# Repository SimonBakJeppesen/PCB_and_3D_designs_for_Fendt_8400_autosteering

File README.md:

# 3D_designs_for_Fendt_8400_autosteering
PCB and 3D design

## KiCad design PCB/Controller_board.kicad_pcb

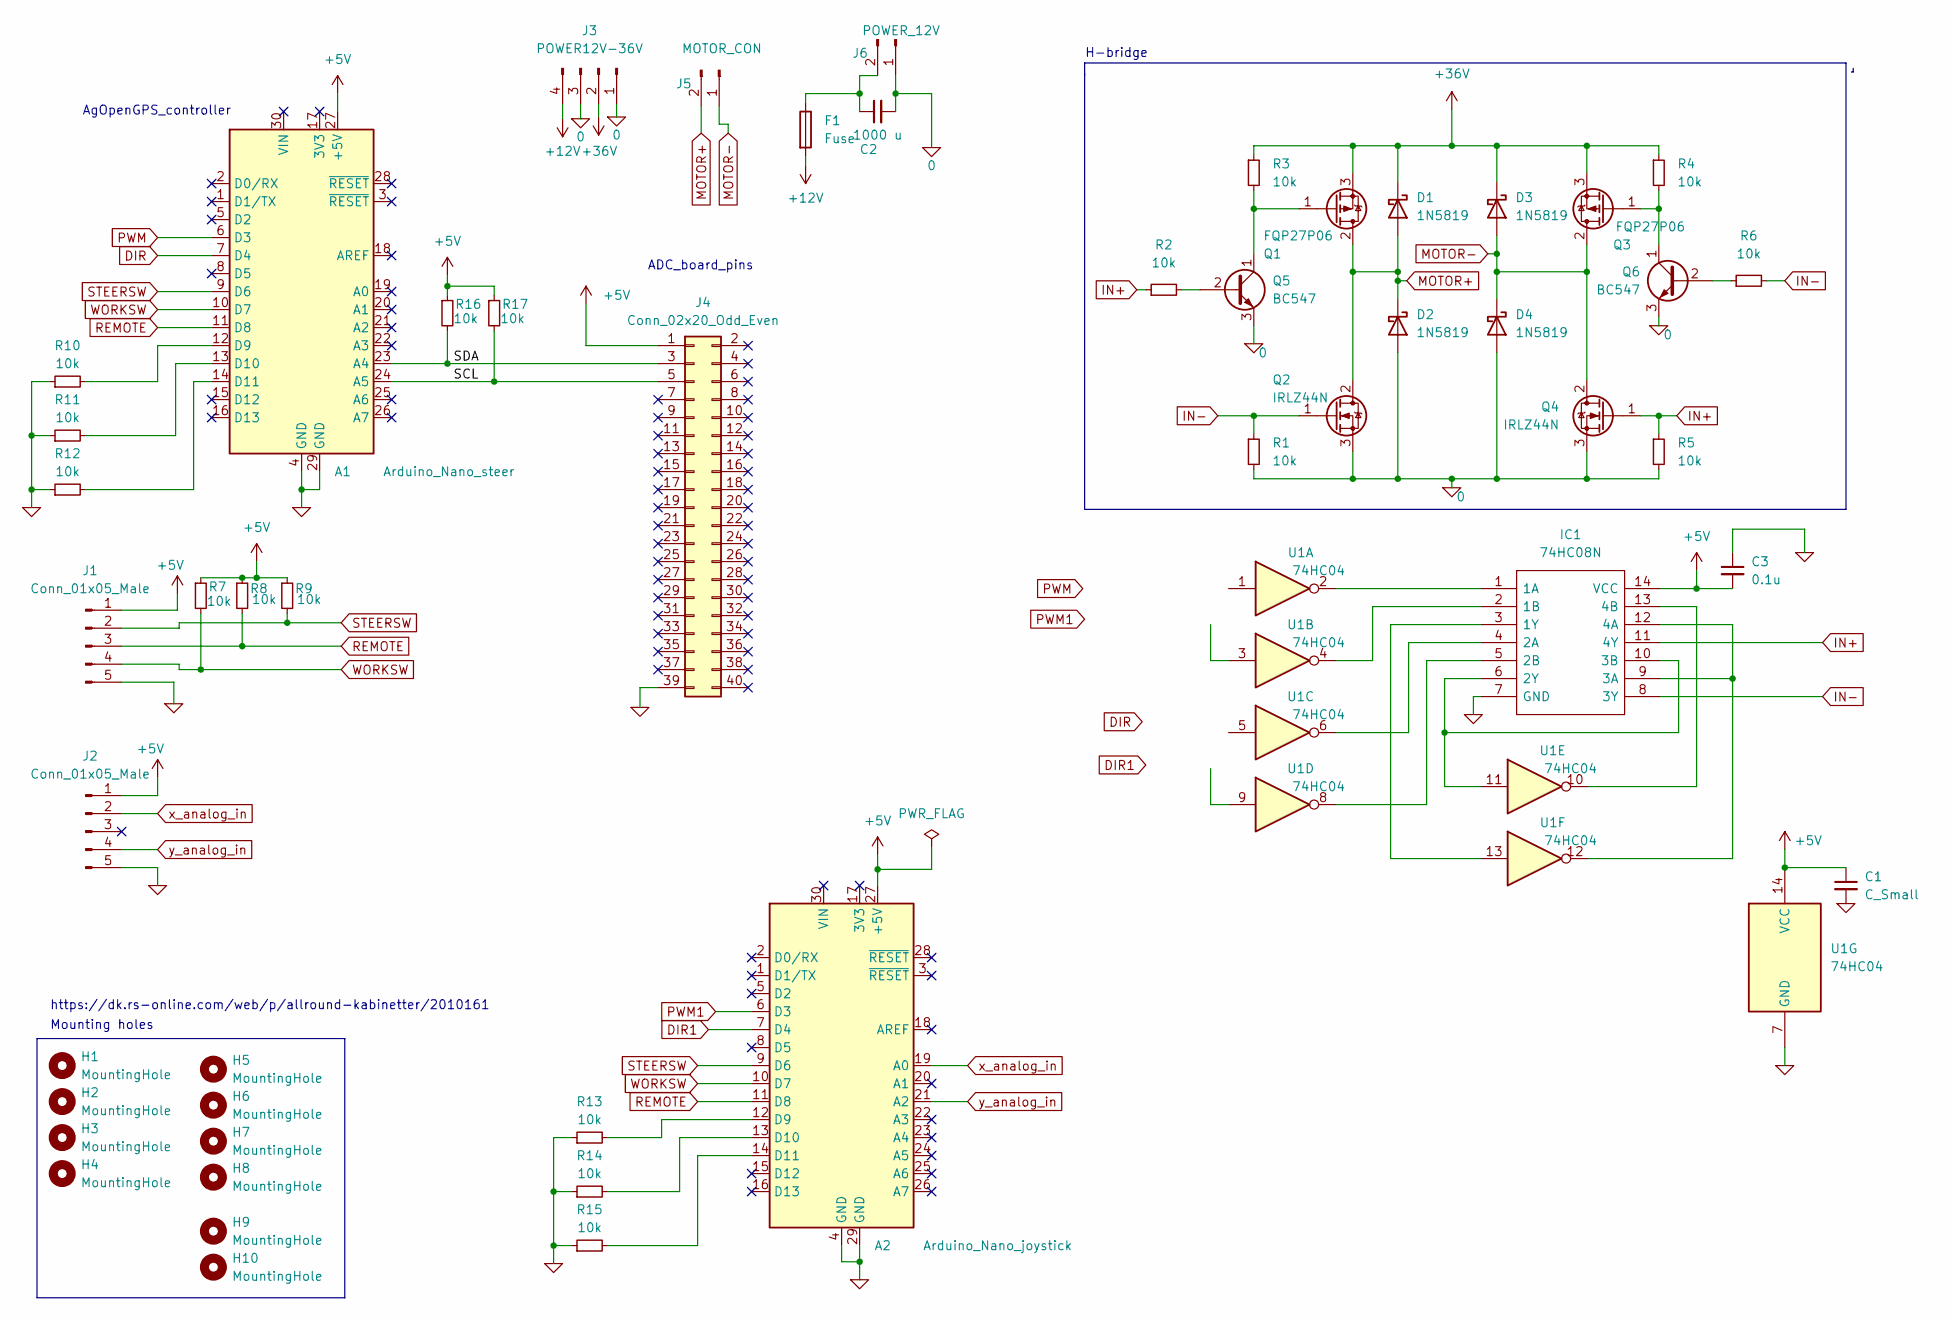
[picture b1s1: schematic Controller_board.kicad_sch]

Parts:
A1: Arduino_Nano_steer; Arduino_Nano
A2: Arduino_Nano_joystick; Arduino_Nano
C1: C_Small; C_Rect_L7.0mm_W3.5mm_P5.00mm
C2: 1000 u; C_Radial_D10.0mm_H12.5mm_P5.00mm
C3: 0.1u; C_Rect_L7.0mm_W3.5mm_P5.00mm
D1, D2, D3, D4: 1N5819; D_DO-41_SOD81_P10.16mm_Horizontal
F1: Fuse; Fuseholder_Cylinder-5x20mm_Stelvio-Kontek_PTF78_Horizontal_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
H1, H2, H3, H4, H5, H6, H7, H8: MountingHole; MountingHole_3mm
H9, H10: MountingHole; MountingHole_5mm
IC1: 74HC08N; DIP-14_W7.62mm; Manufacturer_Part_Number 74HC08N
J1, J2: Conn_01x05_Male; PhoenixContact_MSTBA_2,5_5-G-5,08_1x05_P5.08mm_Horizontal
J3: POWER12V-36V; PhoenixContact_MSTBA_2,5_4-G-5,08_1x04_P5.08mm_Horizontal
J4: Conn_02x20_Odd_Even; PinHeader_2x20_P2.54mm_Vertical
J5: MOTOR_CON; PhoenixContact_MSTBA_2,5_2-G-5,08_1x02_P5.08mm_Horizontal
J6: POWER_12V; PhoenixContact_MSTBA_2,5_2-G-5,08_1x02_P5.08mm_Horizontal
Q1, Q3: FQP27P06; TO-220-3_Vertical
Q2, Q4: IRLZ44N; TO-220-3_Vertical
Q5, Q6: BC547; TO-92_Inline
R1, R2, R3, R4, R5, R6, R7, R8, R9, R10, R11, R12, R13, R14, R15, R16, R17: 10k; R_Axial_DIN0207_L6.3mm_D2.5mm_P7.62mm_Horizontal
U1: 74HC04; DIP-14_W7.62mm

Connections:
0: A1.4 (GND), A1.29 (GND), A2.4 (GND), A2.29 (GND), C1.2, C2.2, C3.1, D2.2 (A), D4.2 (A), IC1.7 (GND), J1.5, J2.5, J3.1, J3.3, J4.39, J6.1, Q2.3 (S), Q4.3 (S), Q5.3 (E), Q6.3 (E), R1.2, R5.2, R10.1, R11.1, R12.1, R13.1, R14.1, R15.1, U1.7 (GND)
+5V: A1.27 (+5V), A2.27 (+5V), C1.1, C3.2, IC1.14 (VCC), J1.1, J2.1, J4.1, R7.1, R8.1, R9.1, R16.1, R17.1, U1.14 (VCC)
+12V: F1.2, J3.4
+36V: D1.1 (K), D3.1 (K), J3.2, Q1.3 (S), Q3.3 (S), R3.1, R4.1
/SCL: A1.24 (A5), J4.5, R17.2
/SDA: A1.23 (A4), J4.3, R16.2
DIR: A1.7 (D4), U1.1
DIR1: A2.7 (D4), U1.3
IN+: IC1.11 (4Y), Q4.1 (G), R2.1, R5.1
IN-: IC1.8 (3Y), Q2.1 (G), R1.1, R6.2
MOTOR+: D1.2 (A), D2.1 (K), J5.2, Q1.2 (D), Q2.2 (D)
MOTOR-: D3.2 (A), D4.1 (K), J5.1, Q3.2 (D), Q4.2 (D)
unnamed: A1.12 (D9), R10.2
unnamed: A1.13 (D10), R11.2
unnamed: A1.14 (D11), R12.2
unnamed: A2.12 (D9), R13.2
unnamed: A2.13 (D10), R14.2
unnamed: A2.14 (D11), R15.2
unnamed: C2.1, F1.1, J6.2
unnamed: IC1.1 (1A), U1.2
unnamed: IC1.2 (1B), U1.4
unnamed: IC1.3 (1Y), U1.13
unnamed: IC1.4 (2A), U1.6
unnamed: IC1.5 (2B), U1.8
unnamed: IC1.6 (2Y), IC1.10 (3B), U1.11
unnamed: IC1.9 (3A), IC1.12 (4A), U1.12
unnamed: IC1.13 (4B), U1.10
unnamed: Q1.1 (G), Q5.1 (C), R3.2
unnamed: Q3.1 (G), Q6.1 (C), R4.2
unnamed: Q5.2 (B), R2.2
unnamed: Q6.2 (B), R6.1
PWM: A1.6 (D3), U1.5
PWM1: A2.6 (D3), U1.9
REMOTE: A1.11 (D8), A2.11 (D8), J1.3, R8.2
STEERSW: A1.9 (D6), A2.9 (D6), J1.2, R9.2
WORKSW: A1.10 (D7), A2.10 (D7), J1.4, R7.2
x_analog_in: A2.19 (A0), J2.2
y_analog_in: A2.21 (A2), J2.4

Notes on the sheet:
Mounting holes
ADC_board_pins
https://dk.rs-online.com/web/p/allround-kabinetter/2010161
AgOpenGPS_controller
H-bridge

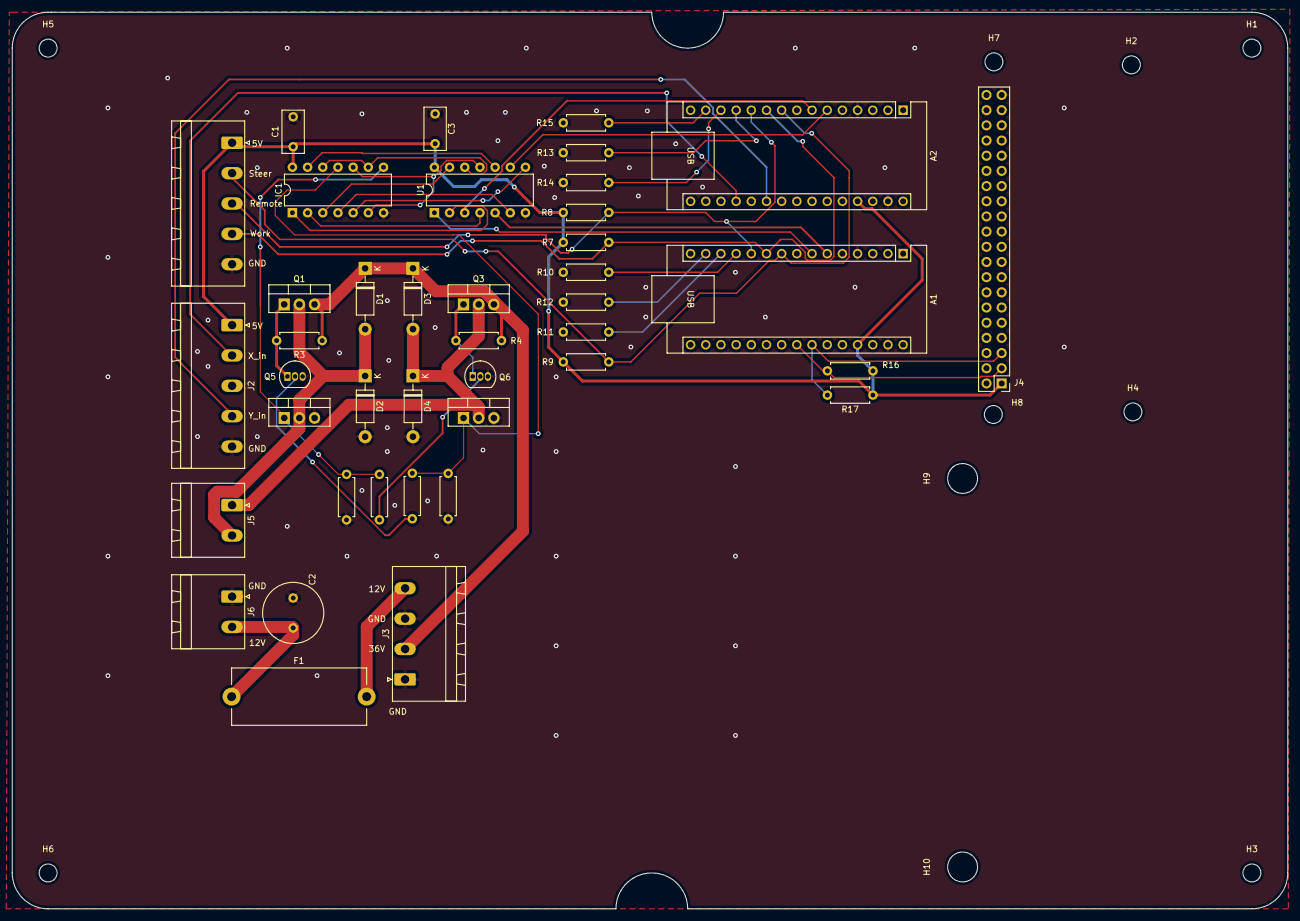
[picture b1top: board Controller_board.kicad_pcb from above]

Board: 2 copper layers, 213.4 x 150.0 mm, 51 parts (0 on the bottom side), 38 nets.

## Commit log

2023-03-24 Added stl and pcb files
2023-03-24 Images
